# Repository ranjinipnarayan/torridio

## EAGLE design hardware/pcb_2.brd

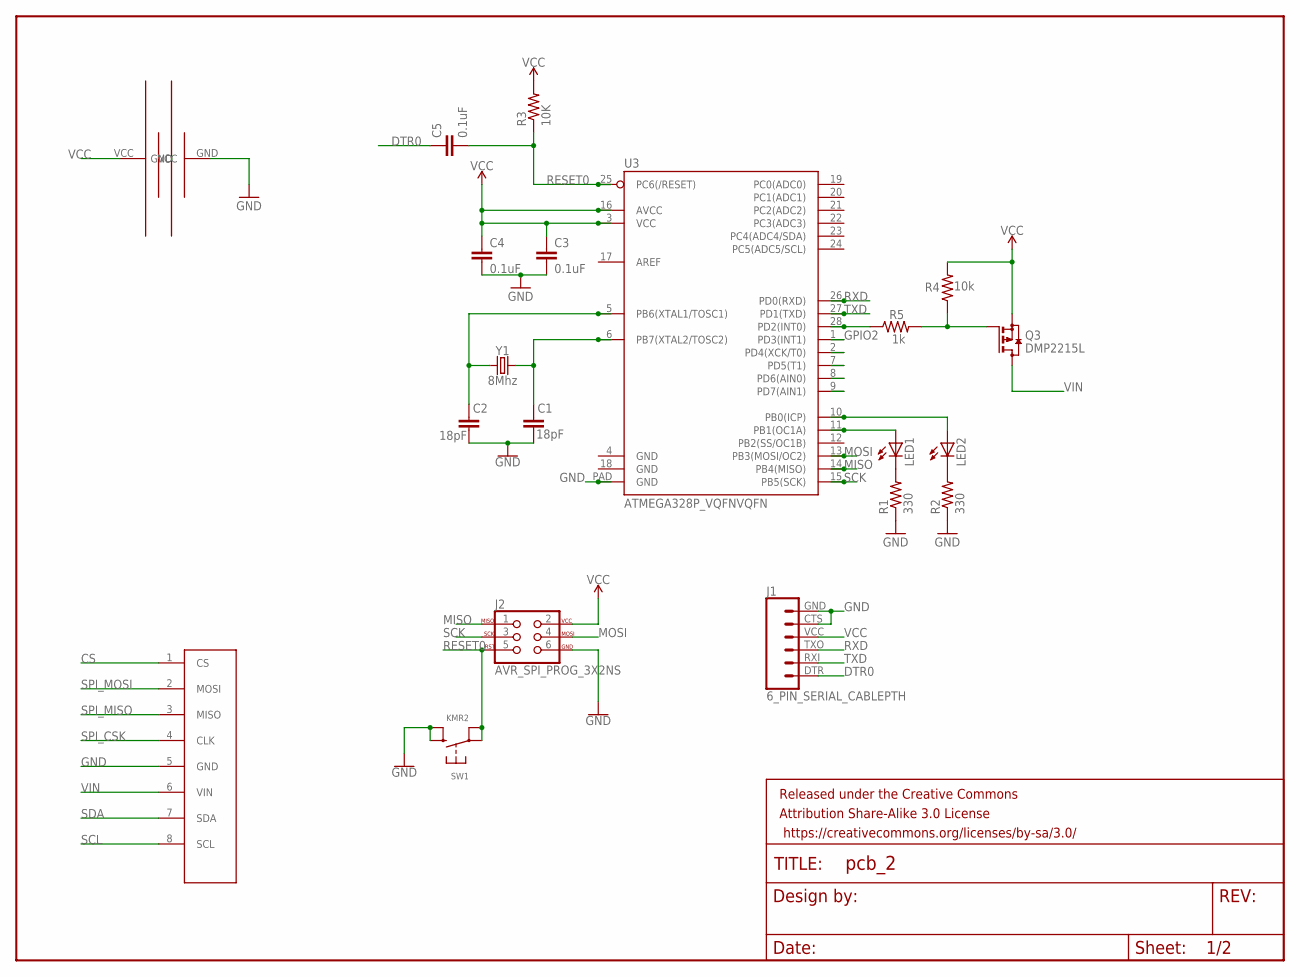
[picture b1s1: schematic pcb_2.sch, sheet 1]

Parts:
C1, C2: 18pF; C0603K
C3, C4, C5: 0.1uF; C0603K
FRAME1: FRAME-LETTER; CREATIVE_COMMONS
J1: 6_PIN_SERIAL_CABLEPTH; FTDI_BASIC
J2: AVR_SPI_PROG_3X2NS; 2X3-NS
LED1, LED2: LED1206; LED-1206
Q3: DMP2215L; SOT23
R1, R2: 330; R0603
R3: 10K; R0603
R4: 10k; R0603
R5: 1k; R0603
SW1: KMR2; BTN_KMR2_4.6X2.8
U3: ATMEGA328P_VQFNVQFN; VQFN-28
U$1: BATTERY; D_PACKAGE
U$6: FLIRFLIR; 1X08_LONGPADS
Y1: 8Mhz; HC49UP

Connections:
CS: U$6.1 (CS)
DTR0: C5.1, J1.DTR (1)
FETEN: Q3.1 (G), R4.1, R5.2
GND: C1.2, C2.2, C3.2, C4.2, J1.CTS (5), J1.GND (6), J2.6, R1.1, R2.1, SW1.B (S), SW1.B' (S1), U3.PAD (GND), U$1.GND, U$6.5 (GND); also elsewhere on the board
GPIO2: U3.1 (PD3(INT1)); also elsewhere on the board
MISO: J2.1, U3.14 (PB4(MISO))
MOSI: J2.4, U3.13 (PB3(MOSI/OC2))
unnamed: LED1.C, R1.2
unnamed: LED1.A, U3.11 (PB1(OC1A))
unnamed: LED2.A, U3.10 (PB0(ICP))
unnamed: LED2.C, R2.2
unnamed: R5.1, U3.28 (PD2(INT0))
unnamed: C1.1, U3.6 (PB7(XTAL2/TOSC2)), Y1.2
unnamed: C2.1, U3.5 (PB6(XTAL1/TOSC1)), Y1.1
RESET0: C5.2, J2.5, R3.1, SW1.A, SW1.A' (P1), U3.25 (PC6(/RESET))
RXD: J1.TXO (3), U3.26 (PD0(RXD))
SCK: J2.3, U3.15 (PB5(SCK))
SCL: U$6.8 (SCL); also elsewhere on the board
SDA: U$6.7 (SDA); also elsewhere on the board
SPI_CSK: U$6.4 (CLK); also elsewhere on the board
SPI_MISO: U$6.3 (MISO); also elsewhere on the board
SPI_MOSI: U$6.2 (MOSI); also elsewhere on the board
TXD: J1.RXI (2), U3.27 (PD1(TXD))
VCC: C3.1, C4.1, J1.VCC (4), J2.2, Q3.2 (S), R3.2, R4.2, U3.3 (VCC), U3.16 (AVCC), U$1.VCC
VIN: Q3.3 (D), U$6.6 (VIN); also elsewhere on the board

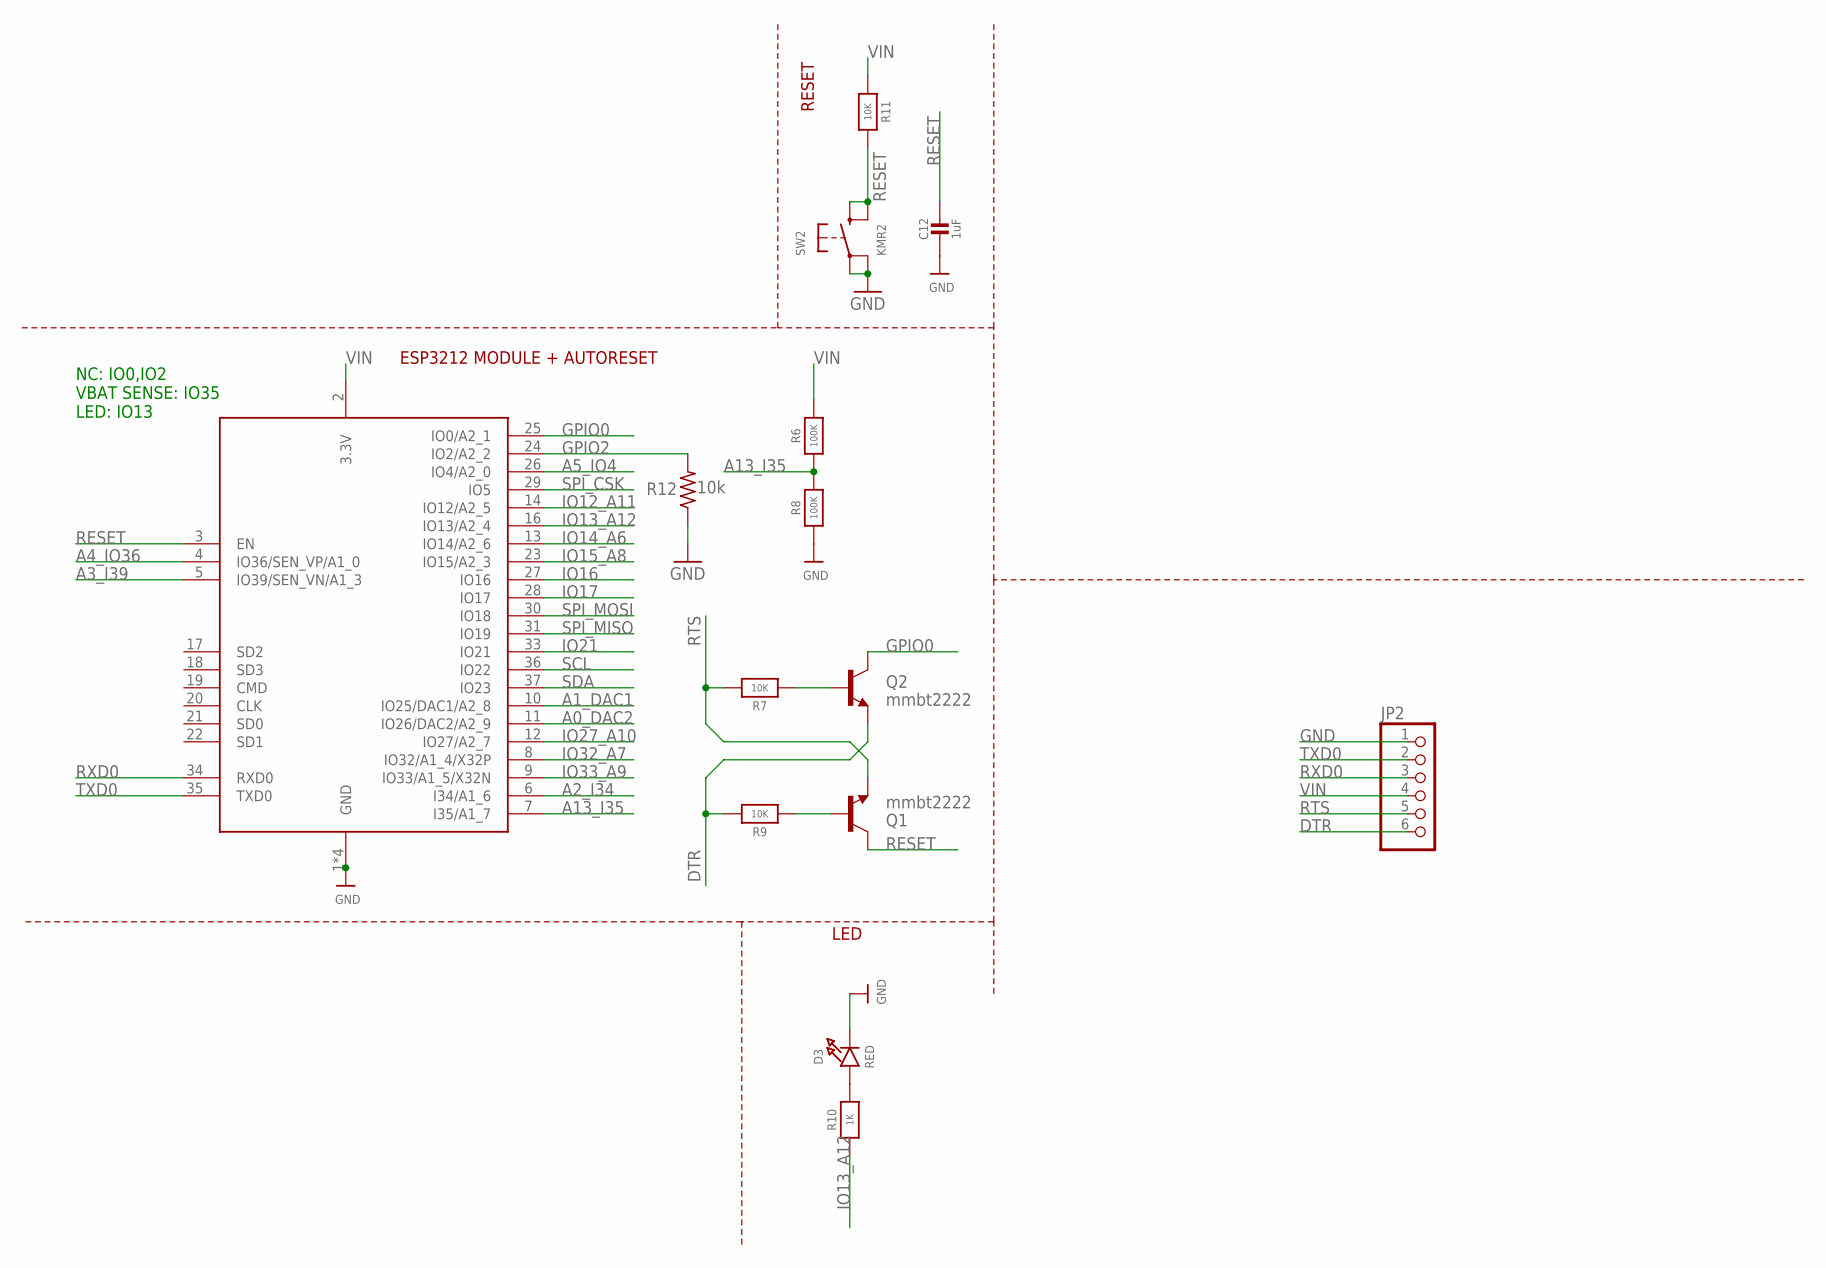
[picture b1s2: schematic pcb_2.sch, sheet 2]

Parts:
C12: 1uF; 0603-NO
D3: RED; CHIPLED_0805_NOOUTLINE
JP2: PINHD-1X6; 1X06
Q1, Q2: mmbt2222; SOT23-3
R6, R8: 100K; 0603-NO
R7, R9, R11: 10K; 0603-NO
R10: 1K; 0603-NO
R12: 10k; R0603
SW2: KMR2; BTN_KMR2_4.6X2.8
X2: ESP32_WROOM32_SKINNY; WROOM32_SKINNY

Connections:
A0_DAC2: X2.11 (IO26/DAC2/A2_9)
A1_DAC1: X2.10 (IO25/DAC1/A2_8)
A2_I34: X2.6 (I34/A1_6)
A3_I39: X2.5 (IO39/SEN_VN/A1_3)
A4_IO36: X2.4 (IO36/SEN_VP/A1_0)
A5_IO4: X2.26 (IO4/A2_0)
A13_I35: R6.1, R8.2, X2.7 (I35/A1_7)
DTR: JP2.6, Q2.2 (E), R9.2
GND: C12.2, D3.C, JP2.1, R8.1, R12.1, SW2.A, SW2.A' (P1), X2.1 (GND), X2.15 (GND), X2.38 (GND), X2.P$1 (GND); also elsewhere on the board
GPIO0: Q2.3 (C), X2.25 (IO0/A2_1)
GPIO2: R12.2, X2.24 (IO2/A2_2); also elsewhere on the board
IO12_A11: X2.14 (IO12/A2_5)
IO13_A12: R10.1, X2.16 (IO13/A2_4)
IO14_A6: X2.13 (IO14/A2_6)
IO15_A8: X2.23 (IO15/A2_3)
IO16: X2.27 (IO16)
IO17: X2.28 (IO17)
IO21: X2.33 (IO21)
IO27_A10: X2.12 (IO27/A2_7)
IO32_A7: X2.8 (IO32/A1_4/X32P)
IO33_A9: X2.9 (IO33/A1_5/X32N)
unnamed: Q1.1 (B), R9.1
unnamed: Q2.1 (B), R7.1
unnamed: D3.A, R10.2
RESET: C12.1, Q1.3 (C), R11.2, SW2.B (S), SW2.B' (S1), X2.3 (EN)
RTS: JP2.5, Q1.2 (E), R7.2
RXD0: JP2.3, X2.34 (RXD0)
SCL: X2.36 (IO22); also elsewhere on the board
SDA: X2.37 (IO23); also elsewhere on the board
SPI_CSK: X2.29 (IO5); also elsewhere on the board
SPI_MISO: X2.31 (IO19); also elsewhere on the board
SPI_MOSI: X2.30 (IO18); also elsewhere on the board
TXD0: JP2.2, X2.35 (TXD0)
VIN: JP2.4, R6.2, R11.1, X2.2 (3.3V); also elsewhere on the board

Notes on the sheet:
RESET
LED
ESP3212 MODULE + AUTORESET
NC: IO0,IO2 VBAT SENSE: IO35 LED: IO13

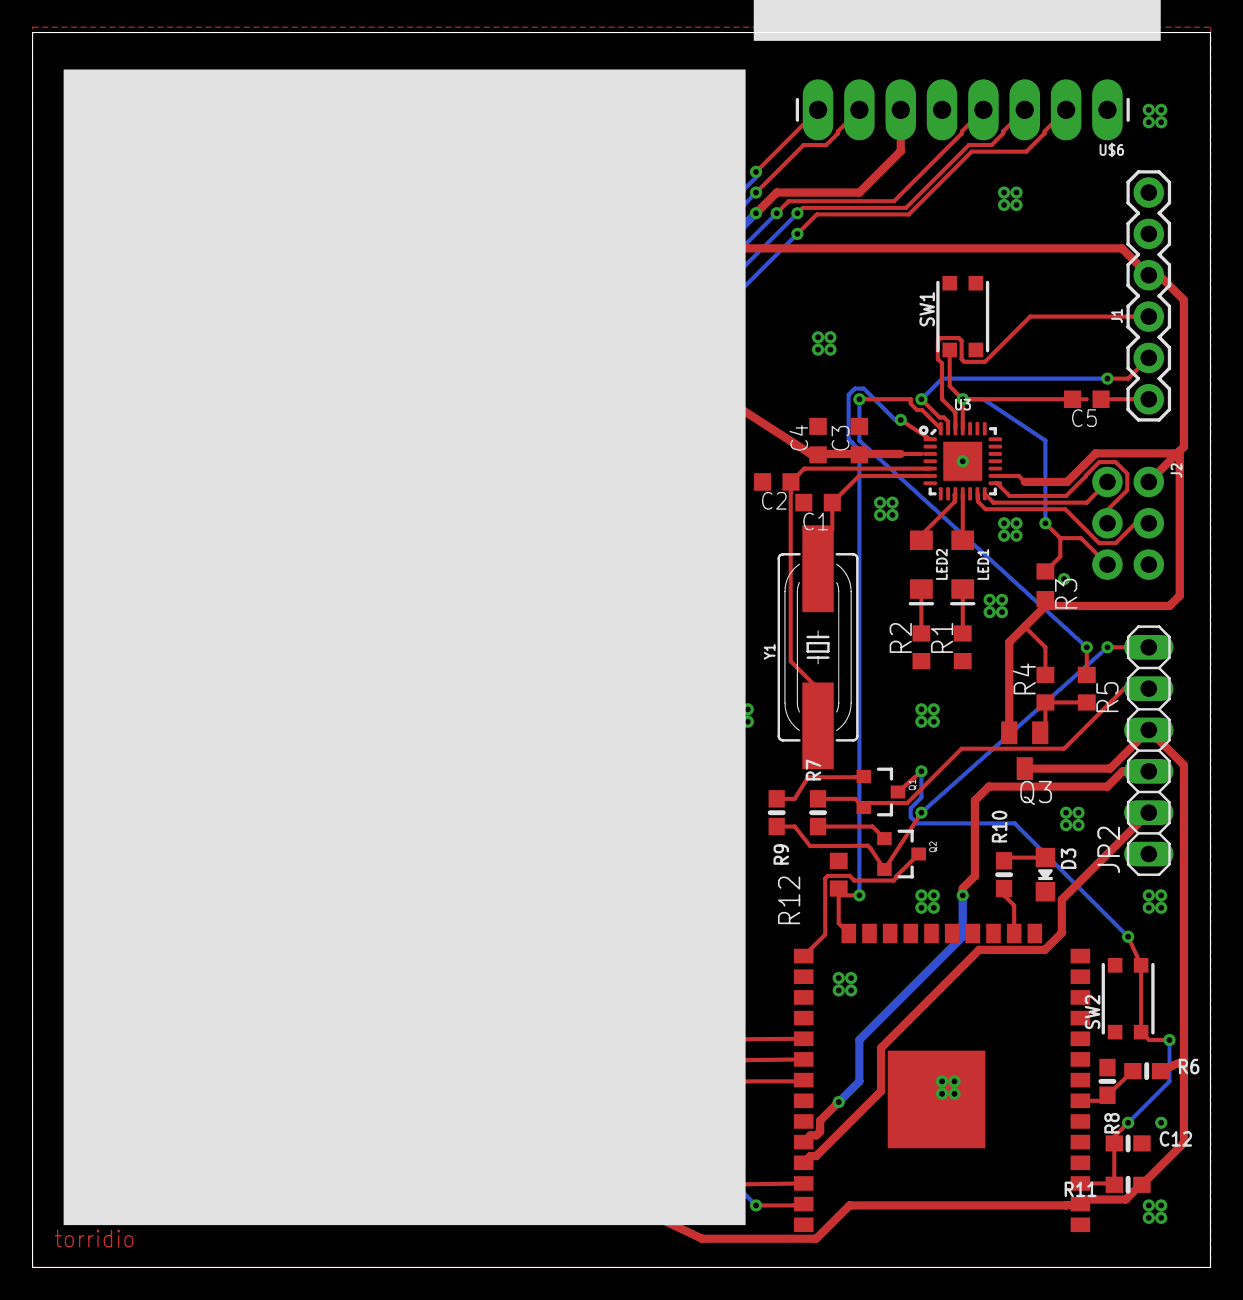
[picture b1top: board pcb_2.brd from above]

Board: 2 copper layers, 72.4 x 75.9 mm, 35 parts (0 on the bottom side), 35 nets.

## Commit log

2018-04-10 flir code
2018-05-01 spi + wifi not working
2018-05-14 final code
2018-05-14 ignoring .DS_store

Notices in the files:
parts and their libraries:
microbuilder: This work is placed in the public domain, and may be freely used for commercial and non-commercial work with the following conditions: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
SparkFun-Retired: Licensing: Creative Commons ShareAlike 4.0 International - https://creativecommons.org/licenses/by-sa/4.0
